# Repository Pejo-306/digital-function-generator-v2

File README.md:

# Цифров генератор на сигнали с тъчскрийн

Генератор на сигнали, реализиран на принципа на Директния Цифров Синтез (DDS).
Проектът е разработен като дипломна работа в 12-ти клас, ТУЕС.

## Съдържание

* [Кратко описание](#кратко-описание)
* [Документация](#документация)
* [Инсталиране на управляващия софтуер](#инсталиране-на-управляващия-софтуер)
* [Лиценз](#лиценз)

## Кратко описание

Генераторите на сигнали са изключително полезни лабораторни инструменти за
изследване на други електронни устройства или части от тях. Инструментите се
използват за възпроизвеждане на най-различни електрически сигнали, които служат
като входни сигнали за други устройства.

Цифровите генератори на сигнали са mixed-signal устройства (включват и аналогова,
и цифрова схемотехника, като и двете функционират ръка за ръка), реализирани
посредством DDS система. Тези генератори, както и разработеният за тази дипломна
работа, имат следните възможностти:
- възпроизвеждане на сигнали с произволна форма;
- регулиране на амплитудата на сигнали;
- добавяне на постояннотоково отместване към генерирания сигнал;
- настройване на честотата на сигнала.

Освен това разработеното за дипломната работа устройство използва течнокристален
екран с панел за допир за реализиране на потребителския си интерфейс. По-подробно
описание на употребения тъчскрийн модул може да бъде намерено [тук](http://www.lcdwiki.com/3.2inch_SPI_Module_ILI9341_SKU:MSP3218).

## Документация

Подробна документация на дипломната работа, написана на български език, може да
бъде намерена [тук](docs/bg/Diploma%20Work_Petar%20Nikolov_2020-bg.pdf).

## Инсталиране на управляващия софтуер

Управляващият софтуер е написан на езика *AVR-C* и е разработен за
микроконтролери от серията *ATmega2561*. Освен това софтуерният проект се 
управлява с конзолната програма **make**.

Първоначално е необходимо да се дръпне проекта от GitHub и да се навигира
до папката, съдържаща софтуерния проект:

```bash
$ git clone https://github.com/Pejo-306/digital-function-generator-v2.git
$ cd digital-function-generator-v2/software/DFGv2-Firmware.X/
```

Проектът се компилира с **make** програмата:

```bash
$ make build
```

След това е необходимо да се свърже подходящ програматор към *ATmega2561* и да
се запише управляващата програма в програмната флаш памет на микроконтролера:

```bash
$ make flash
```

Също така е необходимо да се конфигурират определени хардуерни настройки на
*ATmega2561*:

```bash
$ make fuse
```

## Лиценз

Този проект се разпространява с [MIT лиценз](LICENSE).

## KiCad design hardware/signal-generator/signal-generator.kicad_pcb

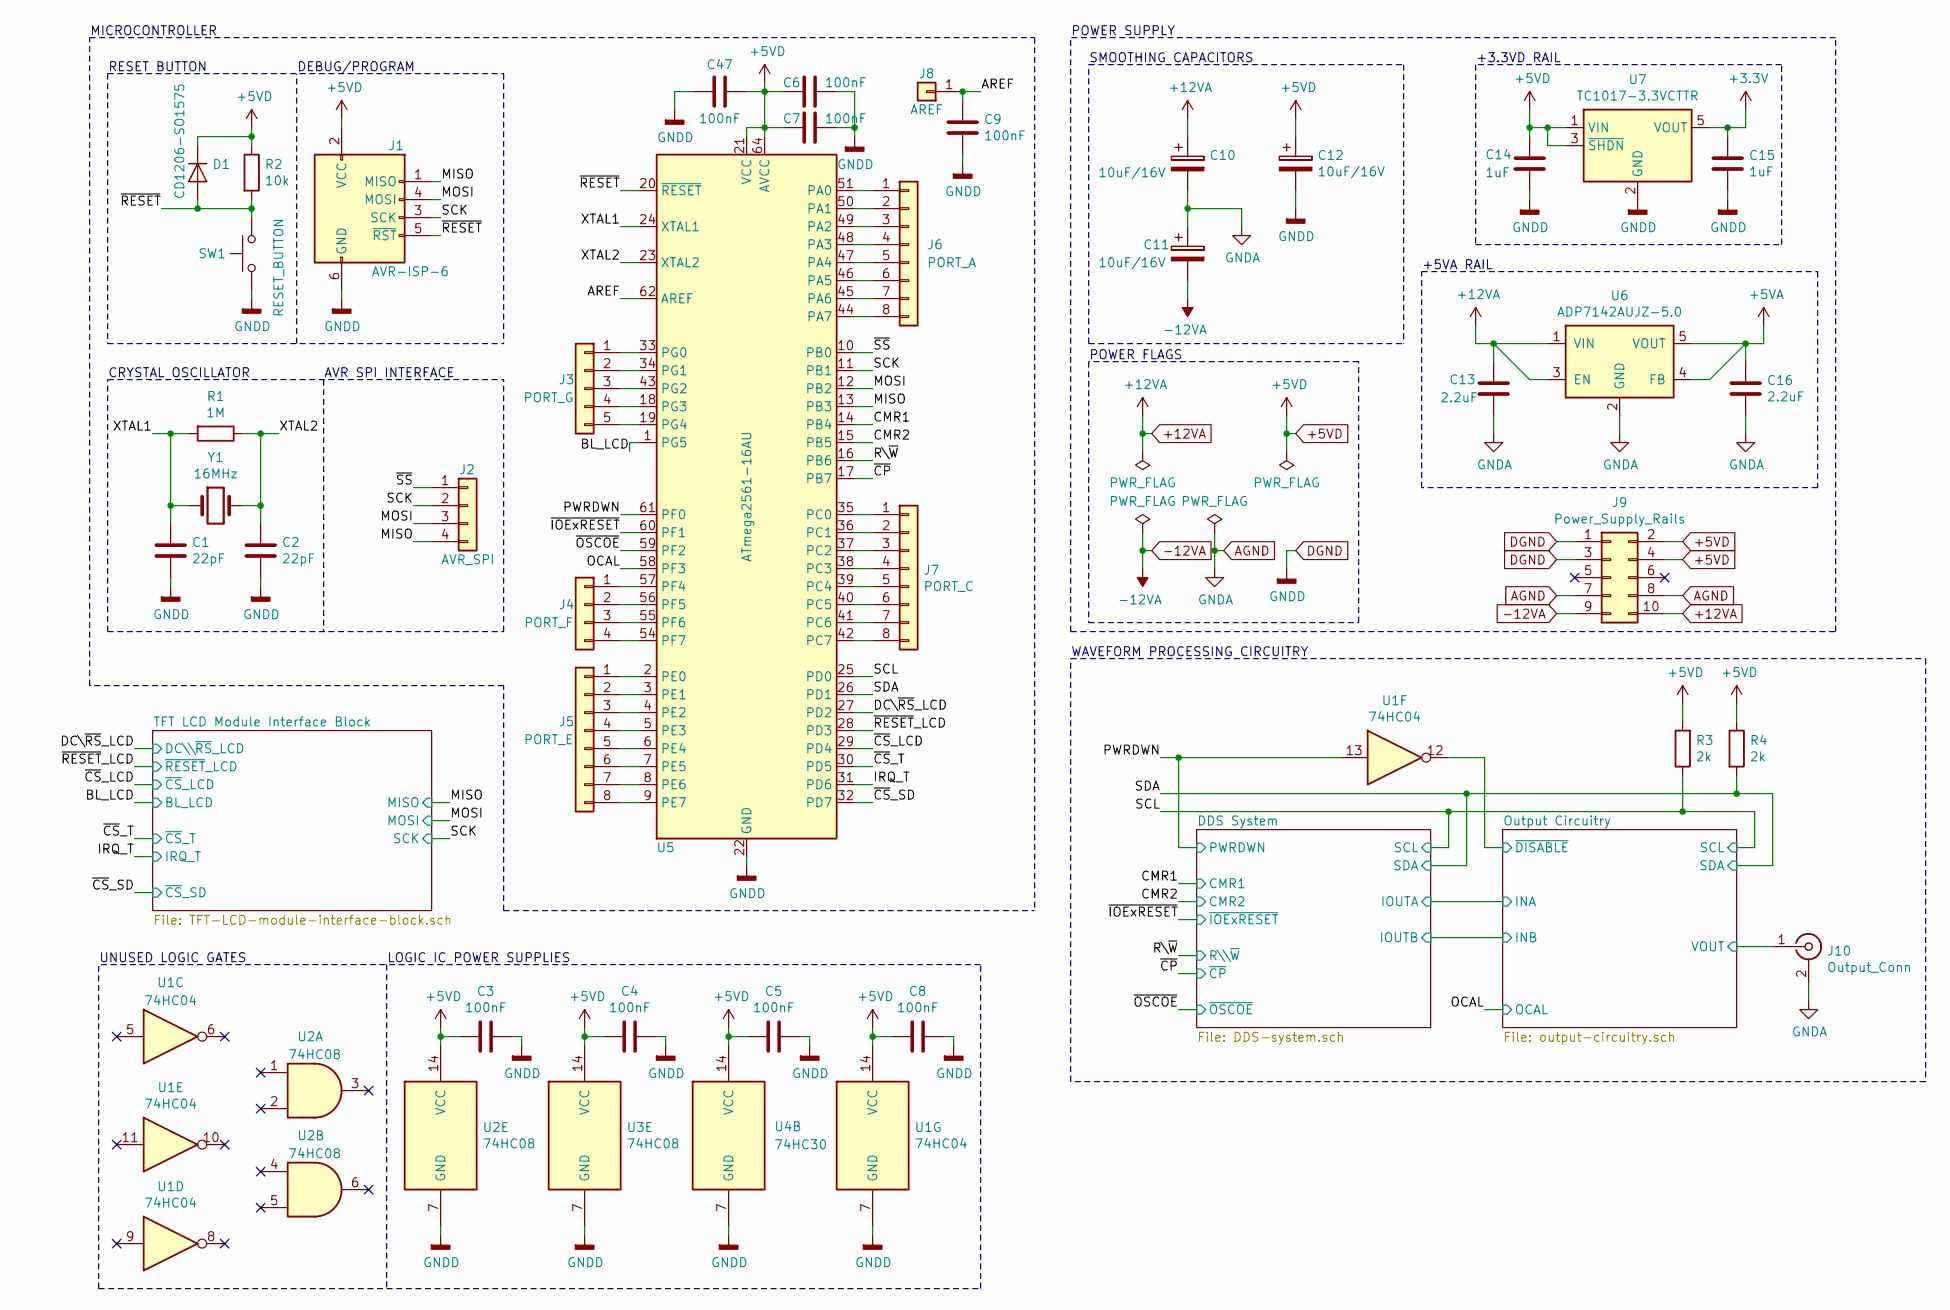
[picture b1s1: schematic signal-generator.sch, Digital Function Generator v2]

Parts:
C1, C2: 22pF; C_0805_HandSoldering
C3, C4, C5, C6, C7, C8, C9, C47: 100nF; C_0805_HandSoldering
C10, C11, C12: 10uF/16V; CP_Elec_4x5.3
C13, C16: 2.2uF; C_0805_HandSoldering
C14, C15: 1uF; C_0805_HandSoldering
D1: CD1206-SO1575; D_1206
J1: AVR-ISP-6; Pin_Header_Straight_2x03_Pitch2.54mm
J2: AVR_SPI; Pin_Header_Straight_1x04_Pitch2.54mm
J3: PORT_G; Pin_Header_Straight_1x05_Pitch2.54mm
J4: PORT_F; Pin_Header_Straight_1x04_Pitch2.54mm
J5: PORT_E; Pin_Header_Straight_1x08_Pitch2.54mm
J6: PORT_A; Pin_Header_Straight_1x08_Pitch2.54mm
J7: PORT_C; Pin_Header_Straight_1x08_Pitch2.54mm
J8: AREF; Pin_Header_Straight_1x01_Pitch2.54mm
J9: Power_Supply_Rails; Pin_Header_Straight_2x05_Pitch2.54mm
J10: Output_Conn; BNC_Socket_TYCO-AMP
R1: 1M; R_1206_HandSoldering
R2: 10k; R_0805_HandSoldering
R3, R4: 2k; R_0805_HandSoldering
SW1: RESET_BUTTON; SW_PUSH_6mm_h4.3mm
U1: 74HC04; SOIC-14_3.9x8.7mm_Pitch1.27mm
U2, U3: 74HC08; SOIC-14_3.9x8.7mm_Pitch1.27mm
U4: 74HC30; SOIC-14_3.9x8.7mm_Pitch1.27mm
U5: ATmega2561-16AU; TQFP-64_14x14mm_Pitch0.8mm
U6: ADP7142AUJZ-5.0; TSOT-23-5_HandSoldering
U7: TC1017-3.3VCTTR; SOT-23-5_HandSoldering
Y1: 16MHz; Crystal_HC49-U_Vertical

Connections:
+3V3: C15.1, U7.5 (VOUT); also elsewhere on the board
+5VA: C16.1, U6.4 (FB), U6.5 (VOUT); also elsewhere on the board
+12VA: C10.1, C13.1, J9.10, U6.1 (VIN), U6.3 (EN); also elsewhere on the board
-12VA: C11.2, J9.9; also elsewhere on the board
/AREF: C9.1, J8.1, U5.62 (AREF)
/BL_LCD: U5.1 (PG5); also elsewhere on the board
/DC\~RS~_LCD: U5.27 (PD2); also elsewhere on the board
/IRQ_T: U5.31 (PD6); also elsewhere on the board
/MISO: J1.1 (MISO), J2.4, U5.13 (PB3); also elsewhere on the board
/MOSI: J1.4 (MOSI), J2.3, U5.12 (PB2); also elsewhere on the board
/OCAL: U5.58 (PF3); also elsewhere on the board
/Output Circuitry/VOUT: J10.1 (In); also elsewhere on the board
/Output Circuitry/~DISABLE: U1.12; also elsewhere on the board
/PWRDWN: U1.13, U5.61 (PF0); also elsewhere on the board
/R\~W: U5.16 (PB6); also elsewhere on the board
/SCK: J1.3 (SCK), J2.2, U5.11 (PB1); also elsewhere on the board
/SCL: R3.1, U5.25 (PD0); also elsewhere on the board
/SDA: R4.2, U5.26 (PD1); also elsewhere on the board
/XTAL1: C1.1, R1.2, U5.24 (XTAL1), Y1.1
/XTAL2: C2.1, R1.1, U5.23 (XTAL2), Y1.2
/~CMR1: U5.14 (PB4); also elsewhere on the board
/~CMR2: U5.15 (PB5); also elsewhere on the board
/~CP: U5.17 (PB7); also elsewhere on the board
/~CS~_LCD: U5.29 (PD4); also elsewhere on the board
/~CS~_SD: U5.32 (PD7); also elsewhere on the board
/~CS~_T: U5.30 (PD5); also elsewhere on the board
/~IOExRESET: U5.60 (PF1); also elsewhere on the board
/~OSCOE: U5.59 (PF2); also elsewhere on the board
/~RESET: D1.2 (A), J1.5 (~RST), R2.2, SW1.2, U5.20 (~RESET)
/~RESET~_LCD: U5.28 (PD3); also elsewhere on the board
/~SS: J2.1, U5.10 (PB0)
unnamed: J3.1, U5.33 (PG0)
unnamed: J3.2, U5.34 (PG1)
unnamed: J3.3, U5.43 (PG2)
unnamed: J3.4, U5.18 (PG3)
unnamed: J3.5, U5.19 (PG4)
unnamed: J4.1, U5.57 (PF4)
unnamed: J4.2, U5.56 (PF5)
unnamed: J4.3, U5.55 (PF6)
unnamed: J4.4, U5.54 (PF7)
unnamed: J5.1, U5.2 (PE0)
unnamed: J5.2, U5.3 (PE1)
unnamed: J5.3, U5.4 (PE2)
unnamed: J5.4, U5.5 (PE3)
unnamed: J5.5, U5.6 (PE4)
unnamed: J5.6, U5.7 (PE5)
unnamed: J5.7, U5.8 (PE6)
unnamed: J5.8, U5.9 (PE7)
unnamed: J6.1, U5.51 (PA0)
unnamed: J6.2, U5.50 (PA1)
unnamed: J6.3, U5.49 (PA2)
unnamed: J6.4, U5.48 (PA3)
unnamed: J6.5, U5.47 (PA4)
unnamed: J6.6, U5.46 (PA5)
unnamed: J6.7, U5.45 (PA6)
unnamed: J6.8, U5.44 (PA7)
unnamed: J7.1, U5.35 (PC0)
unnamed: J7.2, U5.36 (PC1)
unnamed: J7.3, U5.37 (PC2)
unnamed: J7.4, U5.38 (PC3)
unnamed: J7.5, U5.39 (PC4)
unnamed: J7.6, U5.40 (PC5)
unnamed: J7.7, U5.41 (PC6)
unnamed: J7.8, U5.42 (PC7)

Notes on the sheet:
POWER FLAGS
SMOOTHING CAPACITORS
+5VA RAIL
POWER SUPPLY
RESET BUTTON
DEBUG/PROGRAM
CRYSTAL OSCILLATOR
+3.3VD RAIL
AVR SPI INTERFACE
MICROCONTROLLER
WAVEFORM PROCESSING CIRCUITRY
LOGIC IC POWER SUPPLIES
UNUSED LOGIC GATES

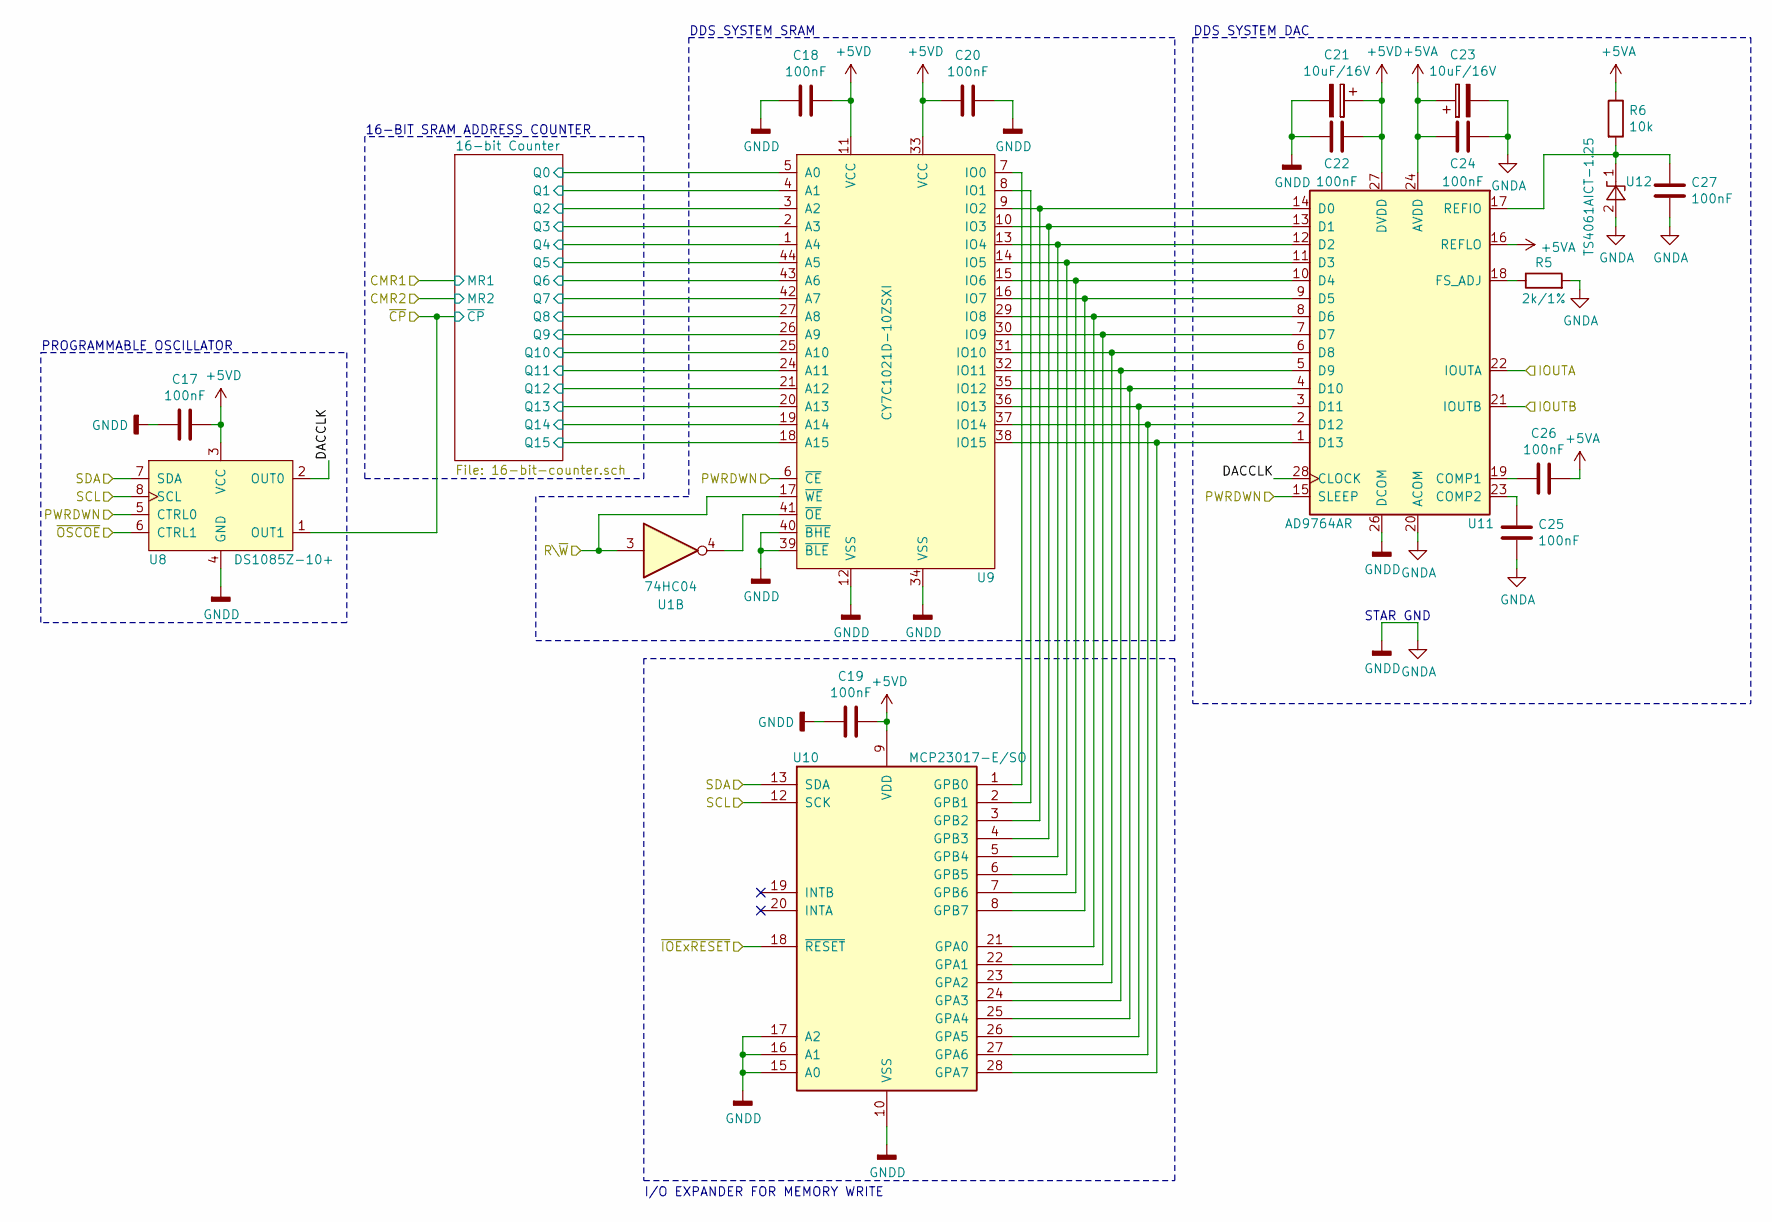
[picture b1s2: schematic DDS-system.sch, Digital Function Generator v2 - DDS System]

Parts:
C17, C18, C19, C20, C22, C24, C25, C26, C27: 100nF; C_0805_HandSoldering
C21, C23: 10uF/16V; CP_Tantalum_Case-A_EIA-3216-18_Hand
R5: 2k/1%; R_0805_HandSoldering
R6: 10k; R_0805_HandSoldering
U1: 74HC04; SOIC-14_3.9x8.7mm_Pitch1.27mm
U8: DS1085Z-10+; SOIC-8_3.9x4.9mm_Pitch1.27mm
U9: CY7C1021D-10ZSXI; SOP80P1176X120-44N
U10: MCP23017-E/SO; SOIC-28W_7.5x17.9mm_Pitch1.27mm
U11: AD9764AR; SOIC-28W_7.5x17.9mm_Pitch1.27mm
U12: TS4061AICT-1.25; SOT-323_SC-70_Handsoldering

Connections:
+5VA: C23.1, C24.2, C26.1, R6.1, U11.16 (REFLO), U11.24 (AVDD); also elsewhere on the board
/DDS System/16-bit Counter/Q0: U9.5 (A0); also elsewhere on the board
/DDS System/16-bit Counter/Q1: U9.4 (A1); also elsewhere on the board
/DDS System/16-bit Counter/Q2: U9.3 (A2); also elsewhere on the board
/DDS System/16-bit Counter/Q3: U9.2 (A3); also elsewhere on the board
/DDS System/16-bit Counter/Q4: U9.1 (A4); also elsewhere on the board
/DDS System/16-bit Counter/Q5: U9.44 (A5); also elsewhere on the board
/DDS System/16-bit Counter/Q6: U9.43 (A6); also elsewhere on the board
/DDS System/16-bit Counter/Q7: U9.42 (A7); also elsewhere on the board
/DDS System/16-bit Counter/Q8: U9.27 (A8); also elsewhere on the board
/DDS System/16-bit Counter/Q9: U9.26 (A9); also elsewhere on the board
/DDS System/16-bit Counter/Q10: U9.25 (A10); also elsewhere on the board
/DDS System/16-bit Counter/Q11: U9.24 (A11); also elsewhere on the board
/DDS System/16-bit Counter/Q12: U9.21 (A12); also elsewhere on the board
/DDS System/16-bit Counter/Q13: U9.20 (A13); also elsewhere on the board
/DDS System/16-bit Counter/Q14: U9.19 (A14); also elsewhere on the board
/DDS System/16-bit Counter/Q15: U9.18 (A15); also elsewhere on the board
/DDS System/DACCLK: U8.2 (OUT0), U11.28 (CLOCK)
/Output Circuitry/INA: U11.22 (IOUTA); also elsewhere on the board
/Output Circuitry/INB: U11.21 (IOUTB); also elsewhere on the board
/PWRDWN: U8.5 (CTRL0), U9.6 (~CE), U11.15 (SLEEP); also elsewhere on the board
/R\~W: U1.3, U9.17 (~WE); also elsewhere on the board
/SCL: U8.8 (SCL), U10.12 (SCK); also elsewhere on the board
/SDA: U8.7 (SDA), U10.13 (SDA); also elsewhere on the board
/~CP: U8.1 (OUT1); also elsewhere on the board
/~IOExRESET: U10.18 (~RESET~); also elsewhere on the board
/~OSCOE: U8.6 (CTRL1); also elsewhere on the board
unnamed: C25.2, U11.23 (COMP2)
unnamed: C26.2, U11.19 (COMP1)
unnamed: C27.1, R6.2, U11.17 (REFIO), U12.1 (K)
unnamed: R5.1, U11.18 (FS_ADJ)
unnamed: U1.4, U9.41 (~OE)
unnamed: U9.7 (IO0), U10.1 (GPB0)
unnamed: U9.8 (IO1), U10.2 (GPB1)
unnamed: U9.9 (IO2), U10.3 (GPB2), U11.14 (D0)
unnamed: U9.10 (IO3), U10.4 (GPB3), U11.13 (D1)
unnamed: U9.13 (IO4), U10.5 (GPB4), U11.12 (D2)
unnamed: U9.14 (IO5), U10.6 (GPB5), U11.11 (D3)
unnamed: U9.15 (IO6), U10.7 (GPB6), U11.10 (D4)
unnamed: U9.16 (IO7), U10.8 (GPB7), U11.9 (D5)
unnamed: U9.29 (IO8), U10.21 (GPA0), U11.8 (D6)
unnamed: U9.30 (IO9), U10.22 (GPA1), U11.7 (D7)
unnamed: U9.31 (IO10), U10.23 (GPA2), U11.6 (D8)
unnamed: U9.32 (IO11), U10.24 (GPA3), U11.5 (D9)
unnamed: U9.35 (IO12), U10.25 (GPA4), U11.4 (D10)
unnamed: U9.36 (IO13), U10.26 (GPA5), U11.3 (D11)
unnamed: U9.37 (IO14), U10.27 (GPA6), U11.2 (D12)
unnamed: U9.38 (IO15), U10.28 (GPA7), U11.1 (D13)

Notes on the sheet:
STAR GND
PROGRAMMABLE OSCILLATOR
I/O EXPANDER FOR MEMORY WRITE
16-BIT SRAM ADDRESS COUNTER
DDS SYSTEM SRAM
DDS SYSTEM DAC

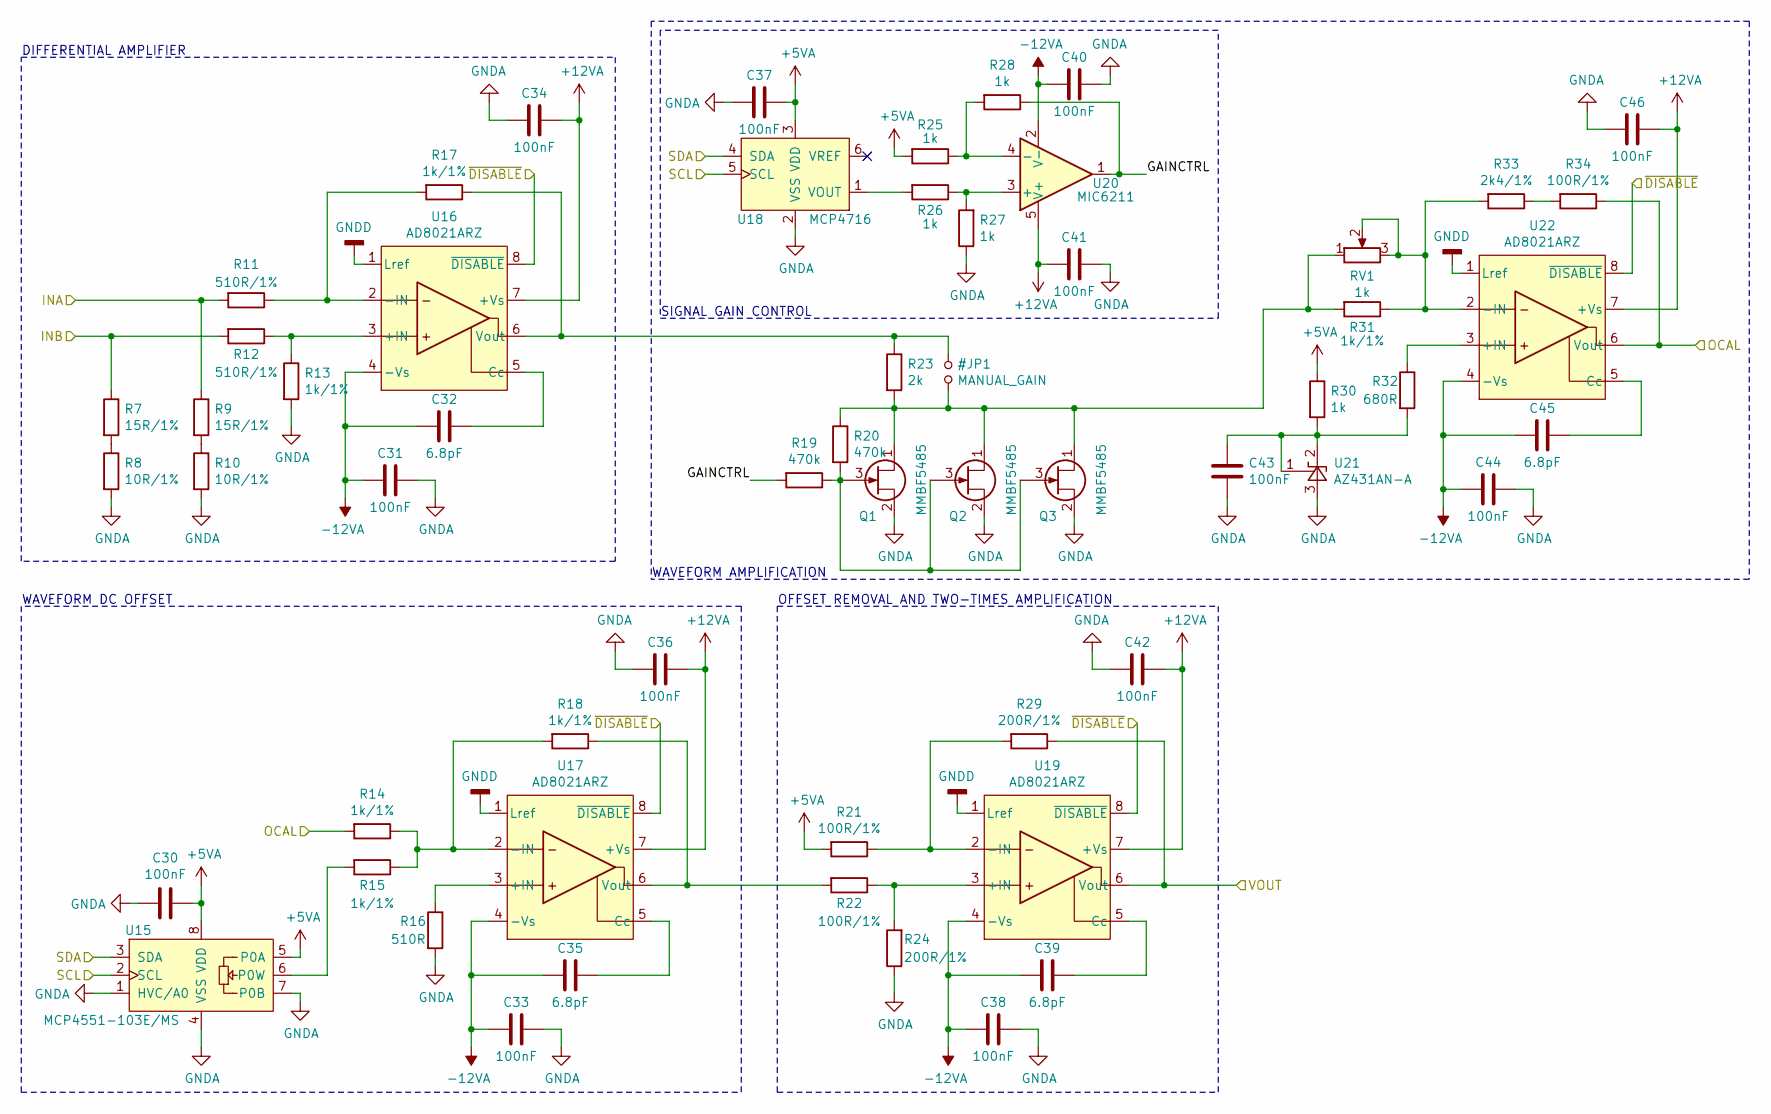
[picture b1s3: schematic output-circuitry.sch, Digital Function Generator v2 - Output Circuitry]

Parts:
C30, C31, C33, C34, C36, C37, C38, C40, C41, C42, C43, C44, C46: 100nF; C_0805_HandSoldering
C32, C35, C39, C45: 6.8pF; C_0805_HandSoldering
Q1, Q2, Q3: MMBF5485; SOT-23_Handsoldering
R7, R9: 15R/1%; R_0805_HandSoldering
R8, R10: 10R/1%; R_0805_HandSoldering
R11, R12: 510R/1%; R_0805_HandSoldering
R13, R14, R15, R17, R18, R31: 1k/1%; R_0805_HandSoldering
R16: 510R; R_0805_HandSoldering
R19, R20: 470k; R_0805_HandSoldering
R21, R22, R34: 100R/1%; R_0805_HandSoldering
R23: 2k; R_0805_HandSoldering
R24, R29: 200R/1%; R_0805_HandSoldering
R25, R26, R27, R28, R30: 1k; R_0805_HandSoldering
R32: 680R; R_0805_HandSoldering
R33: 2k4/1%; R_0805_HandSoldering
RV1: 1k; Potentiometer_Alps_RK163_Single_Vertical
U15: MCP4551-103E/MS; MSOP-8_3x3mm_Pitch0.65mm
U16, U17, U19, U22: AD8021ARZ; SOIC-8_3.9x4.9mm_Pitch1.27mm
U18: MCP4716; SOT-23-6_Handsoldering
U20: MIC6211; SOT-23-5_HandSoldering
U21: AZ431AN-A; SOT-23_Handsoldering

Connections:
+5VA: C30.1, C37.1, R21.2, R25.2, R30.1, U15.5 (P0A), U15.8 (VDD), U18.3 (VDD); also elsewhere on the board
+12VA: C34.1, C36.1, C41.2, C42.1, C46.1, U16.7 (+Vs), U17.7 (+Vs), U19.7 (+Vs), U20.5 (V+), U22.7 (+Vs); also elsewhere on the board
-12VA: C31.2, C32.2, C33.2, C35.2, C38.2, C39.2, C40.2, C44.2, C45.2, U16.4 (-Vs), U17.4 (-Vs), U19.4 (-Vs), U20.2 (V-), U22.4 (-Vs); also elsewhere on the board
/OCAL: R14.2, R34.1, U22.6 (Vout); also elsewhere on the board
/Output Circuitry/GAINCTRL: R19.2, R28.1, U20.1
/Output Circuitry/INA: R9.1, R11.2; also elsewhere on the board
/Output Circuitry/INB: R7.1, R12.2; also elsewhere on the board
/Output Circuitry/VOUT: R29.1, U19.6 (Vout); also elsewhere on the board
/Output Circuitry/~DISABLE: U16.8 (~DISABLE), U17.8 (~DISABLE), U19.8 (~DISABLE), U22.8 (~DISABLE); also elsewhere on the board
/SCL: U15.2 (SCL), U18.5 (SCL); also elsewhere on the board
/SDA: U15.3 (SDA), U18.4 (SDA); also elsewhere on the board
unnamed: C32.1, U16.5 (Cc)
unnamed: C35.1, U17.5 (Cc)
unnamed: C39.1, U19.5 (Cc)
unnamed: C43.1, R30.2, R32.2, U21.1 (REF), U21.2 (K)
unnamed: C45.1, U22.5 (Cc)
unnamed: Q1.3 (G), Q2.3 (G), Q3.3 (G), R19.1, R20.2
unnamed: R7.2, R8.1
unnamed: R9.2, R10.1
unnamed: R11.1, R17.2, U16.2 (-IN)
unnamed: R12.1, R13.1, U16.3 (+IN)
unnamed: R14.1, R15.1, R18.2, U17.2 (-IN)
unnamed: R15.2, U15.6 (P0W)
unnamed: R16.1, U17.3 (+IN)
unnamed: R18.1, R22.2, U17.6 (Vout)
unnamed: R21.1, R29.2, U19.2 (-IN)
unnamed: R22.1, R24.2, U19.3 (+IN)
unnamed: R25.1, R28.2, U20.4 (-)
unnamed: R26.1, R27.2, U20.3 (+)
unnamed: R26.2, U18.1 (VOUT)
unnamed: R31.1, R33.2, RV1.2, RV1.3, U22.2 (-IN)
unnamed: R32.1, U22.3 (+IN)
unnamed: R33.1, R34.2

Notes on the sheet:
DIFFERENTIAL AMPLIFIER
OFFSET REMOVAL AND TWO-TIMES AMPLIFICATION
WAVEFORM DC OFFSET
SIGNAL GAIN CONTROL
WAVEFORM AMPLIFICATION

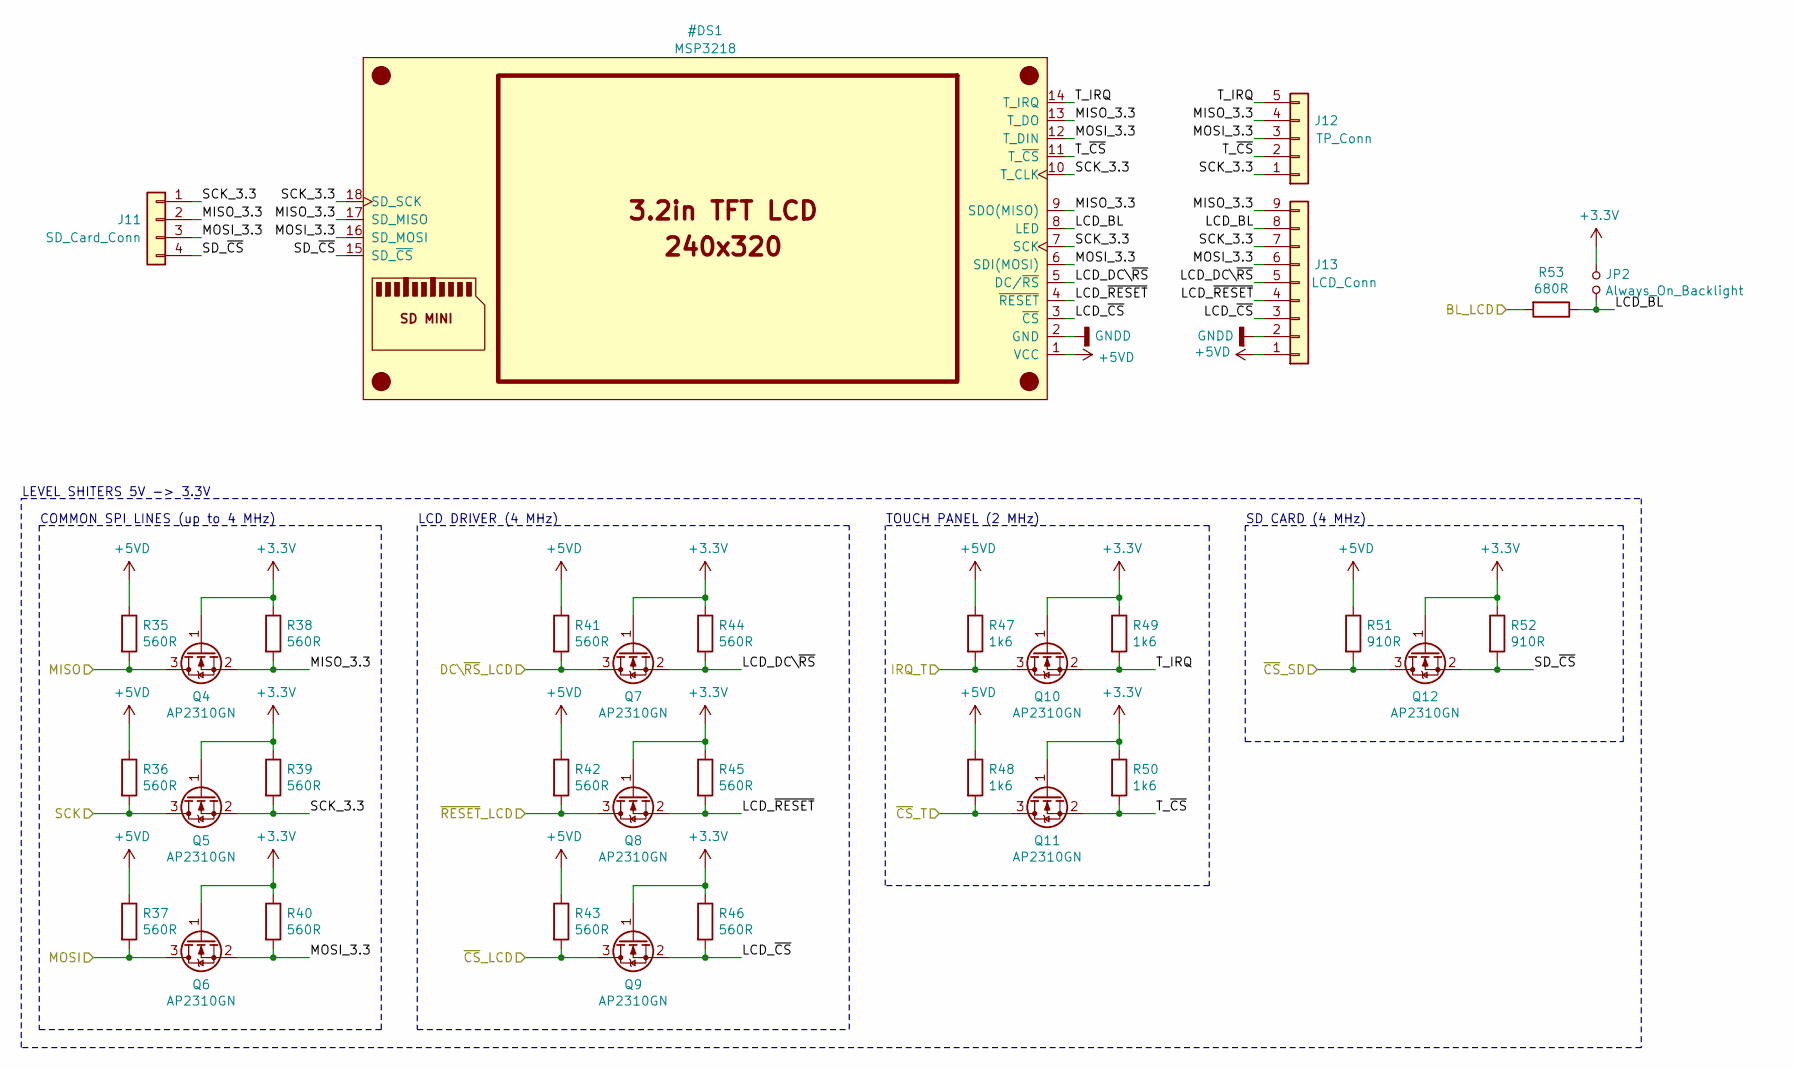
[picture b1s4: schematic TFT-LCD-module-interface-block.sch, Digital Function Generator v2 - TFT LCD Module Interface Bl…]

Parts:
J11: SD_Card_Conn; Pin_Header_Straight_1x04_Pitch2.54mm
J12: TP_Conn; Pin_Header_Straight_1x05_Pitch2.54mm
J13: LCD_Conn; Pin_Header_Straight_1x09_Pitch2.54mm
JP2: Always_On_Backlight; Pin_Header_Straight_1x02_Pitch2.54mm
Q4, Q5, Q6, Q7, Q8, Q9, Q10, Q11, Q12: AP2310GN; SOT-23_Handsoldering
R35, R36, R37, R38, R39, R40, R41, R42, R43, R44, R45, R46: 560R; R_0805_HandSoldering
R47, R48, R49, R50: 1k6; R_0805_HandSoldering
R51, R52: 910R; R_0805_HandSoldering
R53: 680R; R_0805_HandSoldering

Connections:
+3V3: JP2.1, Q4.1, Q5.1, Q6.1, Q7.1, Q8.1, Q9.1, Q10.1, Q11.1, Q12.1, R38.1, R39.1, R40.1, R44.1, R45.1, R46.1, R49.1, R50.1, R52.1; also elsewhere on the board
/BL_LCD: R53.2; also elsewhere on the board
/DC\~RS~_LCD: Q7.3, R41.2; also elsewhere on the board
/IRQ_T: Q10.3, R47.2; also elsewhere on the board
/MISO: Q4.3, R35.2; also elsewhere on the board
/MOSI: Q6.3, R37.2; also elsewhere on the board
/SCK: Q5.3, R36.2; also elsewhere on the board
/~CS~_LCD: Q9.3, R43.2; also elsewhere on the board
/~CS~_SD: Q12.3, R51.2; also elsewhere on the board
/~CS~_T: Q11.3, R48.2; also elsewhere on the board
/~RESET~_LCD: Q8.3, R42.2; also elsewhere on the board

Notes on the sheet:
TOUCH PANEL (2 MHz)
LCD DRIVER (4 MHz)
COMMON SPI LINES (up to 4 MHz)
LEVEL SHITERS 5V -> 3.3V
SD CARD (4 MHz)

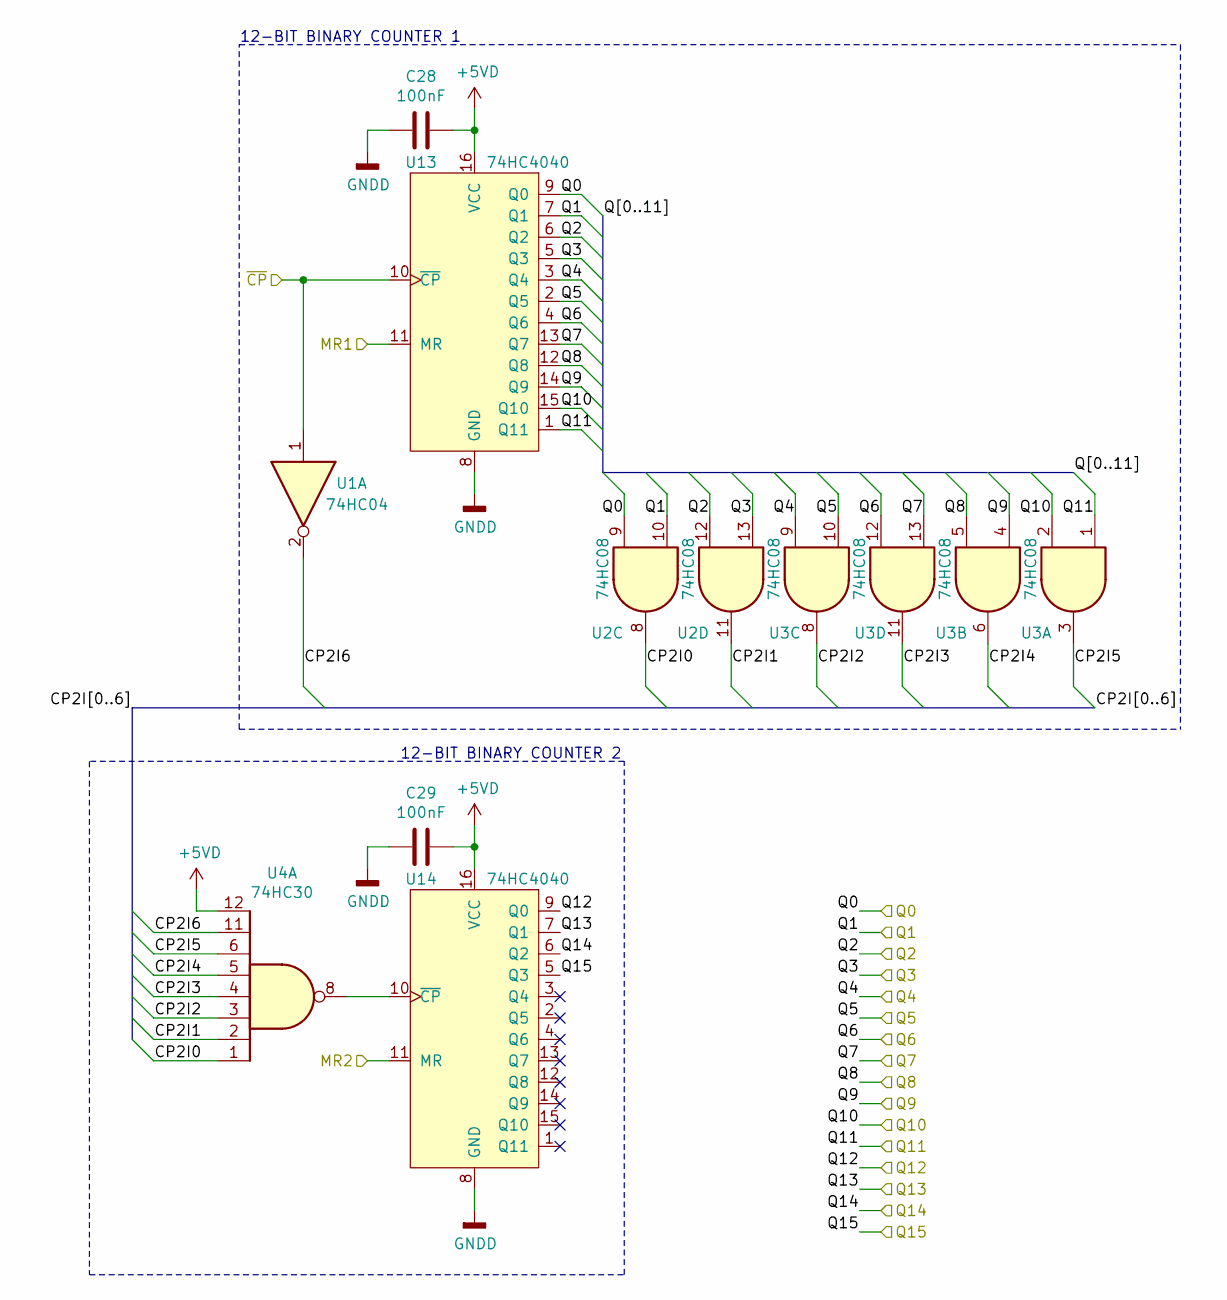
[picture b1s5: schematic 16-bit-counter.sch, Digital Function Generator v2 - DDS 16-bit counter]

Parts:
C28, C29: 100nF; C_0805_HandSoldering
U1: 74HC04; SOIC-14_3.9x8.7mm_Pitch1.27mm
U2, U3: 74HC08; SOIC-14_3.9x8.7mm_Pitch1.27mm
U4: 74HC30; SOIC-14_3.9x8.7mm_Pitch1.27mm
U13, U14: 74HC4040; SOIC-16_3.9x9.9mm_Pitch1.27mm

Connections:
/DDS System/16-bit Counter/CP2I0: U2.8, U4.1
/DDS System/16-bit Counter/CP2I1: U2.11, U4.2
/DDS System/16-bit Counter/CP2I2: U3.8, U4.3
/DDS System/16-bit Counter/CP2I3: U3.11, U4.4
/DDS System/16-bit Counter/CP2I4: U3.6, U4.5
/DDS System/16-bit Counter/CP2I5: U3.3, U4.6
/DDS System/16-bit Counter/CP2I6: U1.2, U4.11
/DDS System/16-bit Counter/Q0: U2.9, U13.9 (Q0); also elsewhere on the board
/DDS System/16-bit Counter/Q1: U2.10, U13.7 (Q1); also elsewhere on the board
/DDS System/16-bit Counter/Q2: U2.12, U13.6 (Q2); also elsewhere on the board
/DDS System/16-bit Counter/Q3: U2.13, U13.5 (Q3); also elsewhere on the board
/DDS System/16-bit Counter/Q4: U3.9, U13.3 (Q4); also elsewhere on the board
/DDS System/16-bit Counter/Q5: U3.10, U13.2 (Q5); also elsewhere on the board
/DDS System/16-bit Counter/Q6: U3.12, U13.4 (Q6); also elsewhere on the board
/DDS System/16-bit Counter/Q7: U3.13, U13.13 (Q7); also elsewhere on the board
/DDS System/16-bit Counter/Q8: U3.5, U13.12 (Q8); also elsewhere on the board
/DDS System/16-bit Counter/Q9: U3.4, U13.14 (Q9); also elsewhere on the board
/DDS System/16-bit Counter/Q10: U3.2, U13.15 (Q10); also elsewhere on the board
/DDS System/16-bit Counter/Q11: U3.1, U13.1 (Q11); also elsewhere on the board
/DDS System/16-bit Counter/Q12: U14.9 (Q0); also elsewhere on the board
/DDS System/16-bit Counter/Q13: U14.7 (Q1); also elsewhere on the board
/DDS System/16-bit Counter/Q14: U14.6 (Q2); also elsewhere on the board
/DDS System/16-bit Counter/Q15: U14.5 (Q3); also elsewhere on the board
/~CMR1: U13.11 (MR); also elsewhere on the board
/~CMR2: U14.11 (MR); also elsewhere on the board
/~CP: U1.1, U13.10 (~CP); also elsewhere on the board
unnamed: U4.8, U14.10 (~CP)

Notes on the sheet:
12-BIT BINARY COUNTER 1
12-BIT BINARY COUNTER 2

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
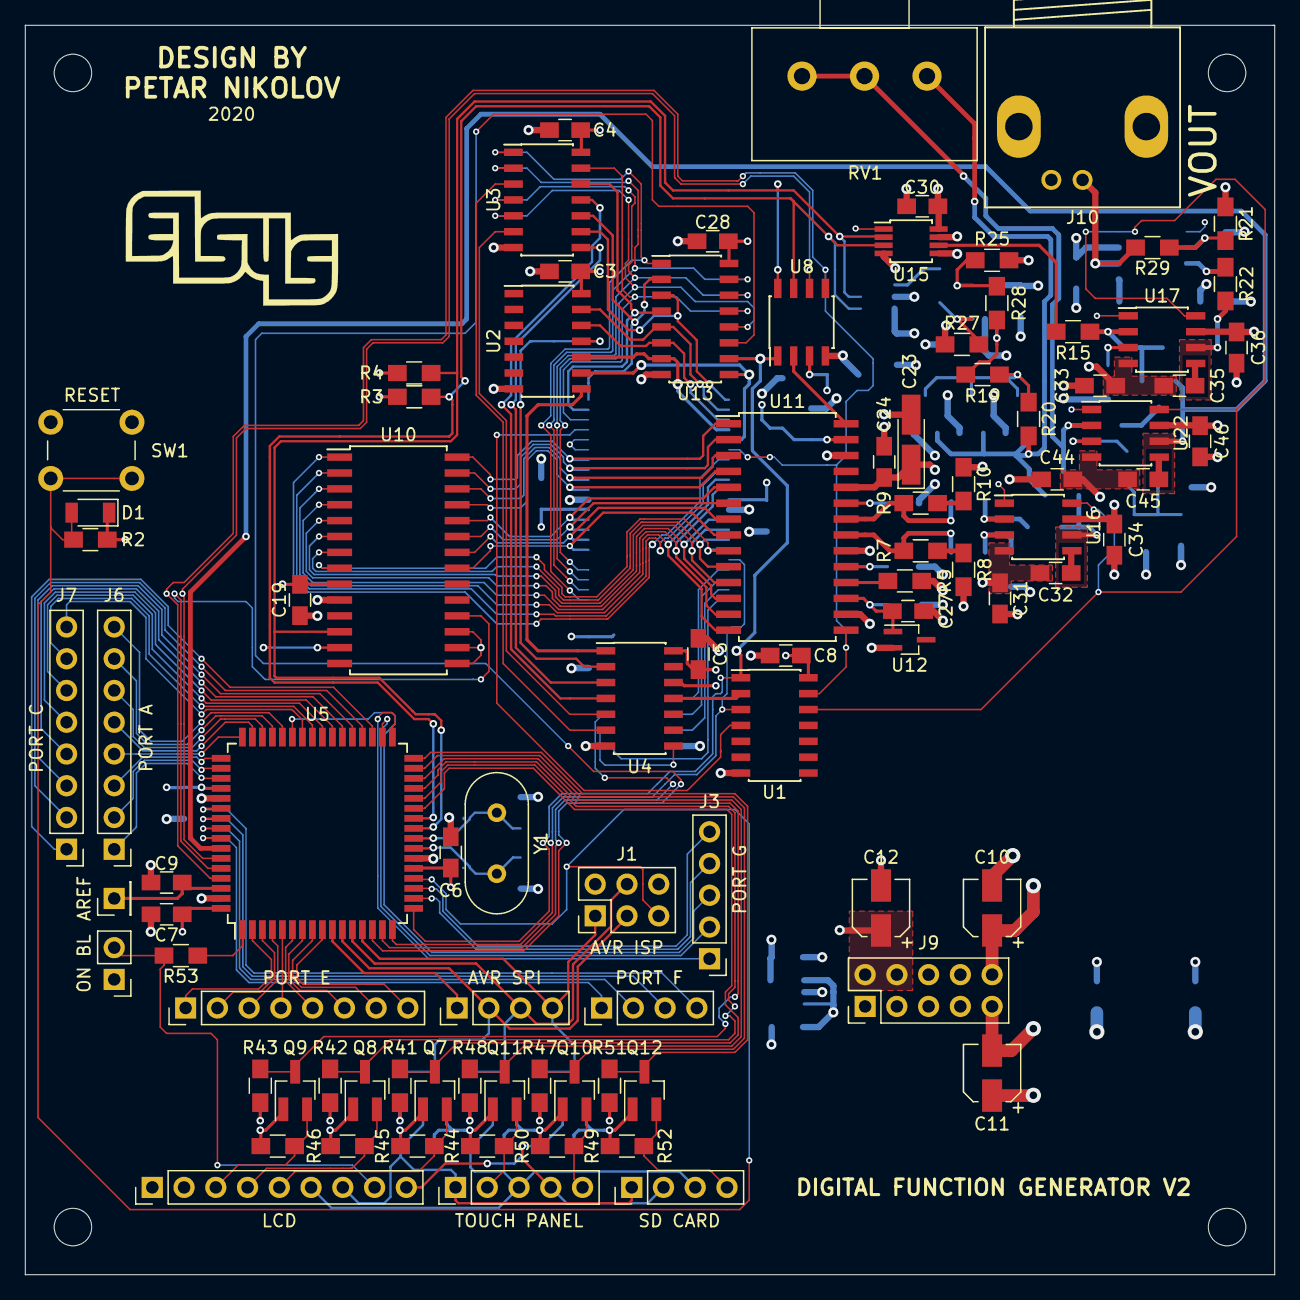
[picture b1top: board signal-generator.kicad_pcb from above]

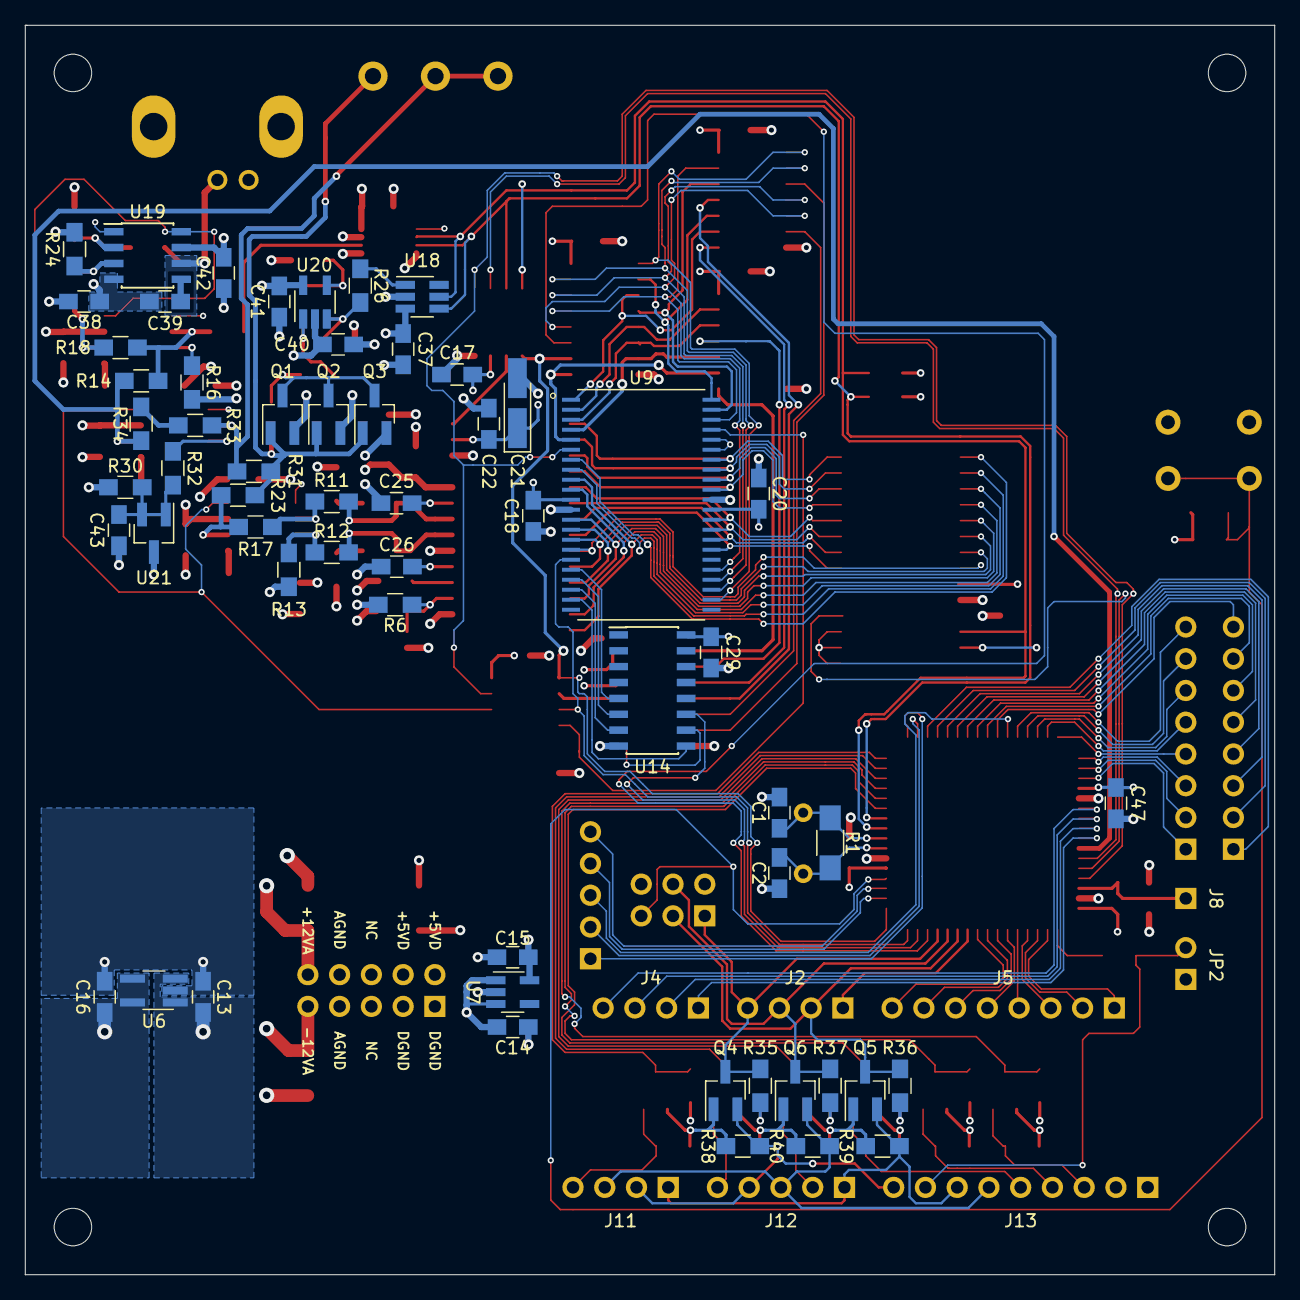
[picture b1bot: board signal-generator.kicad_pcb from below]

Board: 4 copper layers, 99.9 x 99.9 mm, 152 parts (59 on the bottom side), 149 nets.
